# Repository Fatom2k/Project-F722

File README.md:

# Project-F722
Yet Another flight controler for quadcopters based on f722 chipset. 

V0.1:
- 30x30mm form factor
- f722 target betaflight FuryOSD
- icm20602 32khz gyro
- mpu6000 gyro
- osd 7452
- through hole pads
- bec 5v 2a
- bec 3.3v
- fuse and tension invert protection
- up to 6s input

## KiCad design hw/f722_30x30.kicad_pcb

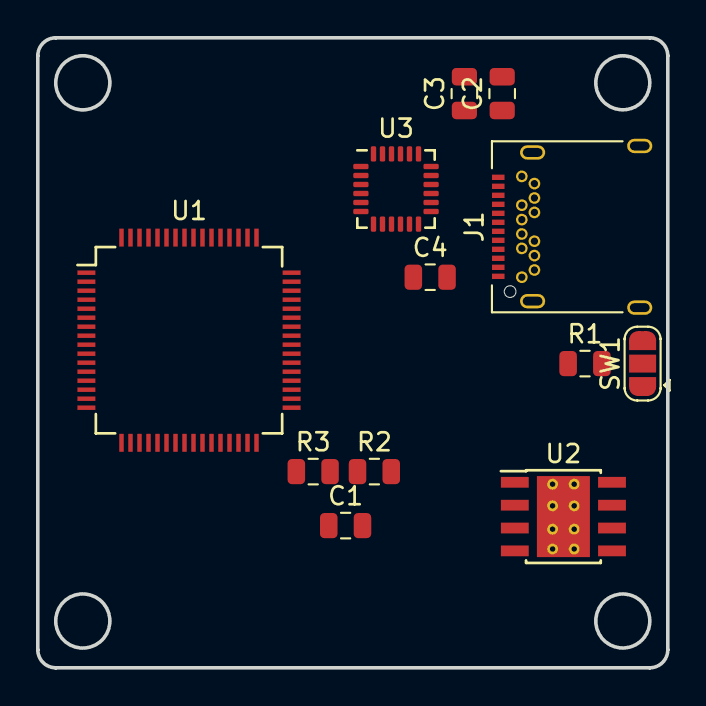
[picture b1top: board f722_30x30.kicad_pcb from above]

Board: 2 copper layers, 35.0 x 35.0 mm, 12 parts (0 on the bottom side), 13 nets, no tracks yet.

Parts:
C1: 10nF; C_0805_2012Metric
C2: 2.2µF; C_0805_2012Metric
C3: 0.1µF; C_0805_2012Metric
C4: C_Small; C_0805_2012Metric
J1: USB_C_Receptacle; USB_C_Receptacle_Amphenol_12401548E4-2A
R1: 4.7k; R_0805_2012Metric
R2, R3: 10k; R_0805_2012Metric
SW1: BOOT; SolderJumper-3_P1.3mm_Open_RoundedPad1.0x1.5mm
U1: STM32F722RETx; LQFP-64_10x10mm_P0.5mm
U2: TPS5430DDA; TI_SO-PowerPAD-8_ThermalVias
U3: MPU-6000; InvenSense_QFN-24_4x4mm_P0.5mm

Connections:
/D+: J1.A6, J1.B6, U1.45
/D-: J1.A7, J1.B7, U1.44
/GYRO_CS: U1.20, U3.8
/MISO1: U1.22, U3.9
/MOSI1: U1.23, U3.24
/SCLK1: U1.21, U3.23
GND: C1.1, C2.2, C3.2, C4.2, R1.2, R3.2, U1.12, U1.18, U1.31, U1.47, U1.63, U3.18
unnamed: C4.1, U3.10
unnamed: J1.A1, J1.A12, J1.B1, J1.B12
unnamed: J1.A4, J1.A9, J1.B4, J1.B9
unnamed: R1.1, SW1.2, U1.60
unnamed: R2.2, R3.1, U1.41
VDD: C1.2, C2.1, C3.1, R2.1, SW1.1, U1.19, U1.32, U1.48, U1.64, U3.13

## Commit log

2019-09-06 update
    Create some directories to store and organize datas
2019-09-06 Create mamba
2019-09-07 add mamba f722 docs
2019-09-07 add useful stuff
2022-01-13 update design
